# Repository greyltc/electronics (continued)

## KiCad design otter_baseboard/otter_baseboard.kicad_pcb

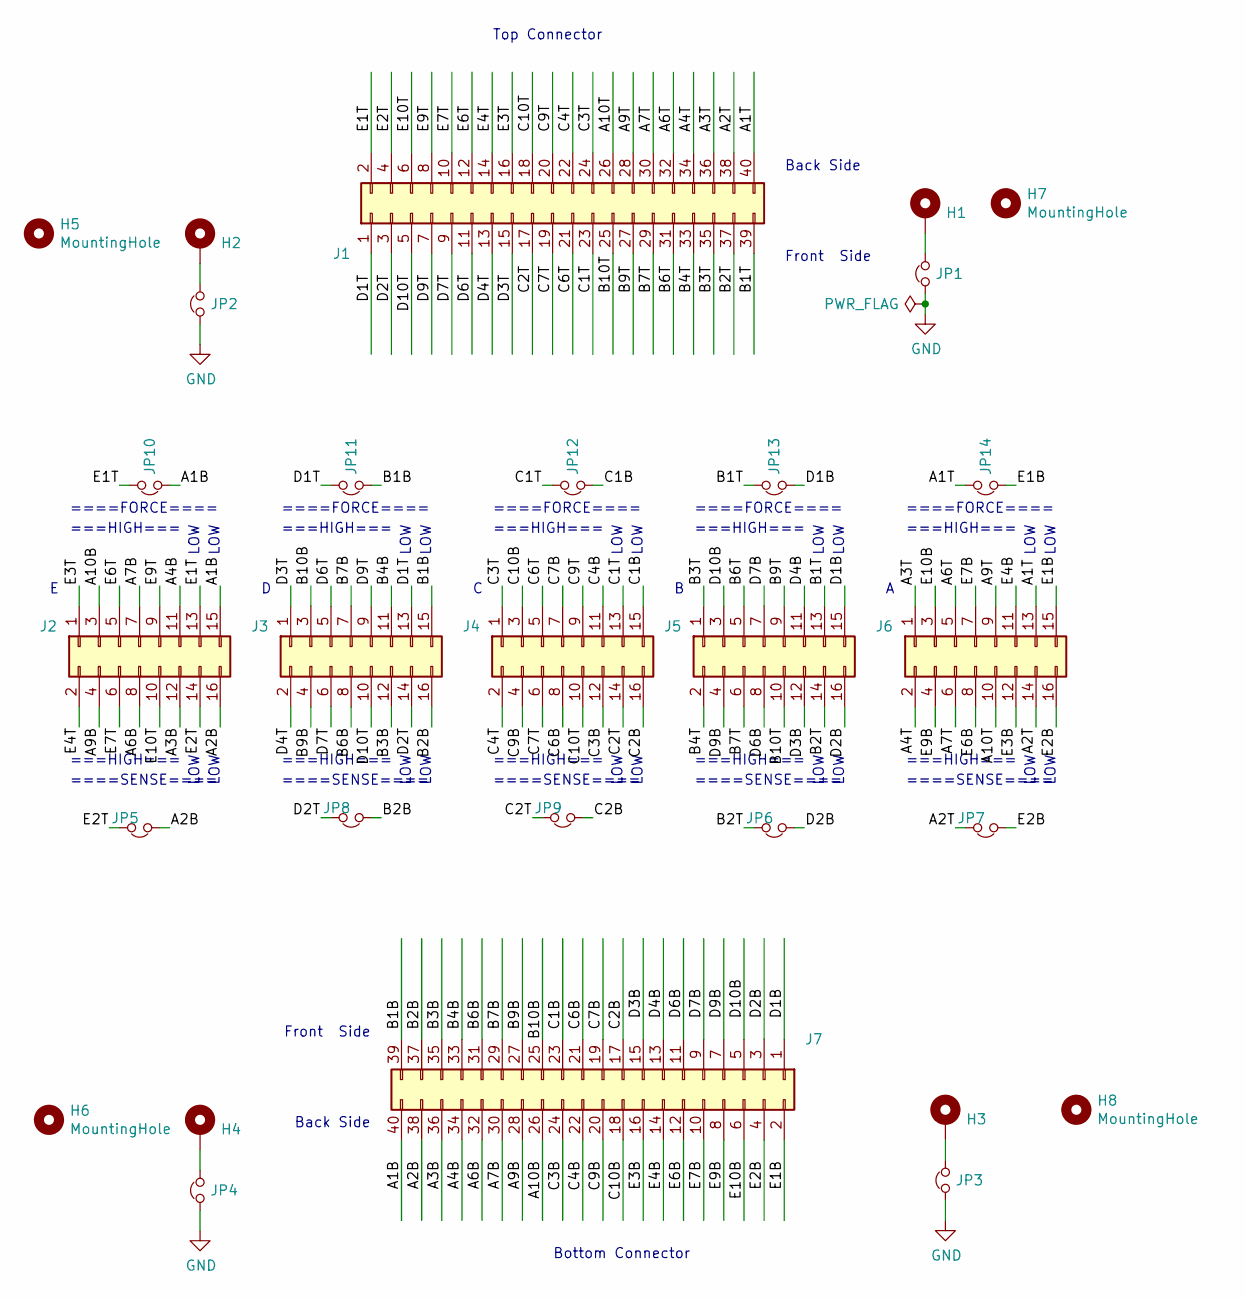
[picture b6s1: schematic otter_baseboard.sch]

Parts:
H1, H2, H3, H4: MountingHole_Pad; MountingHole_3.2mm_M3_ISO7380_Pad
H5, H6, H7, H8: MountingHole; MountingHole_6.4mm_M6
J1, J7: Conn_02x20_Odd_Even; Samtec_MECF-20-01-NP-L-DV-WT_2x20_P1.27mm_Socket_Horizontal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; mfg_part MECF-20-01-L-DV-NP-WT
J2, J3, J4, J5, J6: Conn_02x08_Odd_Even; PinHeader_2x08_P2.54mm_Vertical
JP1, JP2, JP3, JP4, JP5, JP6, JP7, JP8, JP9, JP10, JP11, JP12, JP13, JP14: Jumper_NC_Small; SolderJumper-2_P1.3mm_Bridged_RoundedPad1.0x1.5mm

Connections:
/A1B: J2.15, J7.40, JP10.2
/A1T: J1.40, J6.13, JP14.1
/A2B: J2.16, J7.38, JP5.2
/A2T: J1.38, J6.14, JP7.1
/A3B: J2.12, J7.36
/A3T: J1.36, J6.1
/A4B: J2.11, J7.34
/A4T: J1.34, J6.2
/A6B: J2.8, J7.32
/A6T: J1.32, J6.5
/A7B: J2.7, J7.30
/A7T: J1.30, J6.6
/A9B: J2.4, J7.28
/A9T: J1.28, J6.9
/A10B: J2.3, J7.26
/A10T: J1.26, J6.10
/B1B: J3.15, J7.39, JP11.2
/B1T: J1.39, J5.13, JP13.1
/B2B: J3.16, J7.37, JP8.2
/B2T: J1.37, J5.14, JP6.1
/B3B: J3.12, J7.35
/B3T: J1.35, J5.1
/B4B: J3.11, J7.33
/B4T: J1.33, J5.2
/B6B: J3.8, J7.31
/B6T: J1.31, J5.5
/B7B: J3.7, J7.29
/B7T: J1.29, J5.6
/B9B: J3.4, J7.27
/B9T: J1.27, J5.9
/B10B: J3.3, J7.25
/B10T: J1.25, J5.10
/C1B: J4.15, J7.23, JP12.2
/C1T: J1.23, J4.13, JP12.1
/C2B: J4.16, J7.17, JP9.2
/C2T: J1.17, J4.14, JP9.1
/C3B: J4.12, J7.24
/C3T: J1.24, J4.1
/C4B: J4.11, J7.22
/C4T: J1.22, J4.2
/C6B: J4.8, J7.21
/C6T: J1.21, J4.5
/C7B: J4.7, J7.19
/C7T: J1.19, J4.6
/C9B: J4.4, J7.20
/C9T: J1.20, J4.9
/C10B: J4.3, J7.18
/C10T: J1.18, J4.10
/D1B: J5.15, J7.1, JP13.2
/D1T: J1.1, J3.13, JP11.1
/D2B: J5.16, J7.3, JP6.2
/D2T: J1.3, J3.14, JP8.1
/D3B: J5.12, J7.15
/D3T: J1.15, J3.1
/D4B: J5.11, J7.13
/D4T: J1.13, J3.2
/D6B: J5.8, J7.11
/D6T: J1.11, J3.5
/D7B: J5.7, J7.9
/D7T: J1.9, J3.6
/D9B: J5.4, J7.7
/D9T: J1.7, J3.9
/D10B: J5.3, J7.5
/D10T: J1.5, J3.10
/E1B: J6.15, J7.2, JP14.2
/E1T: J1.2, J2.13, JP10.1
/E2B: J6.16, J7.4, JP7.2
/E2T: J1.4, J2.14, JP5.1
/E3B: J6.12, J7.16
/E3T: J1.16, J2.1
/E4B: J6.11, J7.14
/E4T: J1.14, J2.2
/E6B: J6.8, J7.12
/E6T: J1.12, J2.5
/E7B: J6.7, J7.10
/E7T: J1.10, J2.6
/E9B: J6.4, J7.8
/E9T: J1.8, J2.9
/E10B: J6.3, J7.6
/E10T: J1.6, J2.10
GND: JP1.1, JP2.1, JP3.1, JP4.1
unnamed: H1.1, JP1.2
unnamed: H2.1, JP2.2
unnamed: H3.1, JP3.2
unnamed: H4.1, JP4.2

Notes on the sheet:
LOW
====FORCE====
===HIGH===
====SENSE====
Front Side
Back Side
Bottom Connector
Top Connector

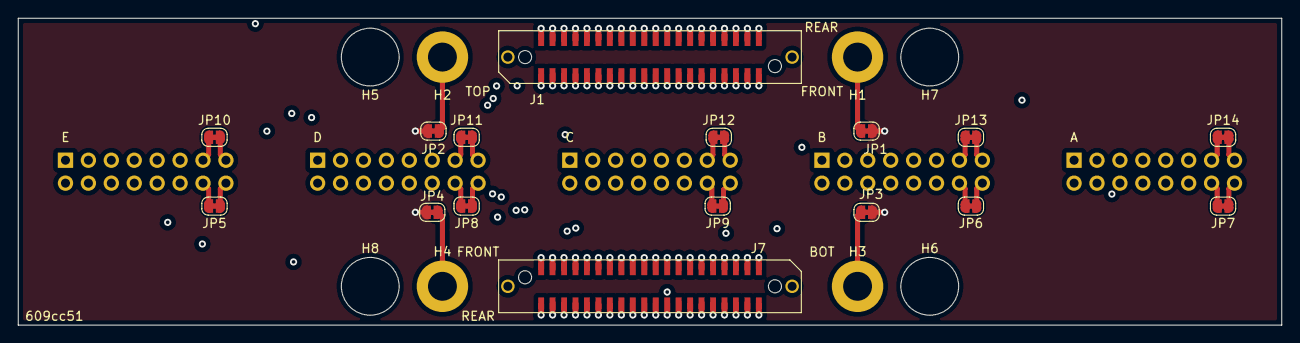
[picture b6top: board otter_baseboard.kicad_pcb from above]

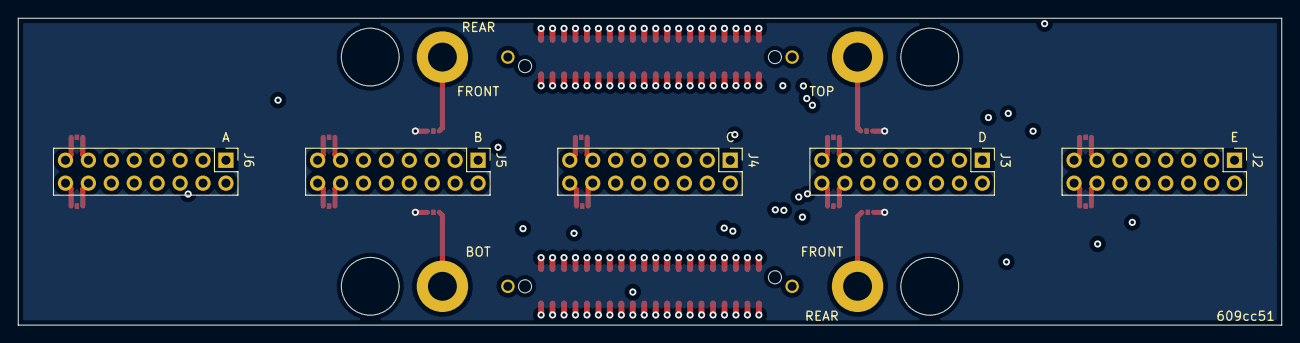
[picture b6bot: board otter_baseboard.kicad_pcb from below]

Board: 4 copper layers, 140.0 x 34.0 mm, 29 parts (5 on the bottom side), 85 nets.

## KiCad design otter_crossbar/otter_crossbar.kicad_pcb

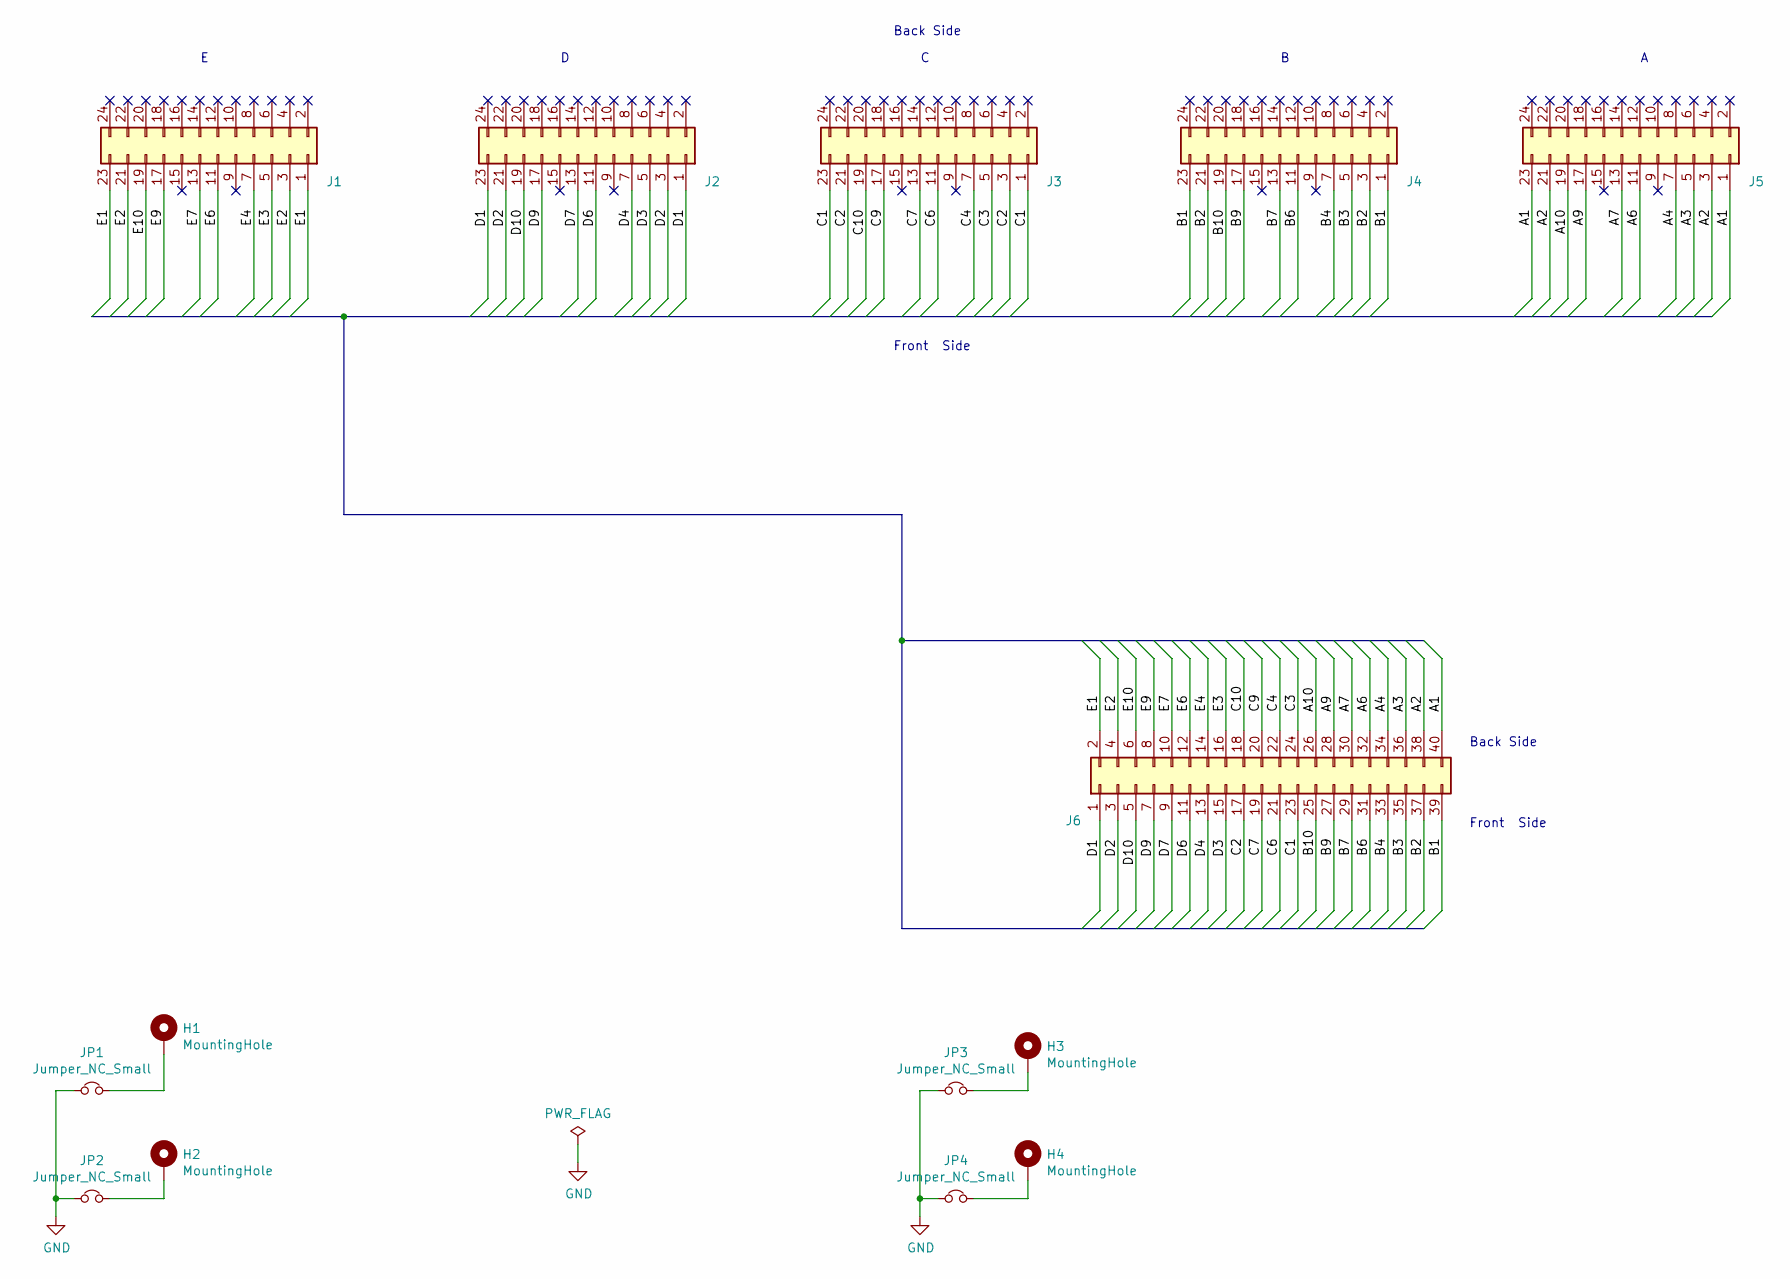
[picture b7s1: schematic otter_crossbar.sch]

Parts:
H1, H2, H3, H4: MountingHole; MountingHole_2.2mm_M2_Pad_Via
J1, J2, J3, J4, J5: Conn_02x12_Counter_Clockwise; PinSocket_2x12_P2.00mm_Vertical_EDGE; mfg_part SQT-112-03-F-D
J6: Conn_02x20_Odd_Even; Samtec_MECF-20-0_-NP-L-DV_2x20_P1.27mm_Edge_mod; mfg_part MECF-20-01-L-DV-NP-WT
JP1, JP2, JP3, JP4: Jumper_NC_Small; SolderJumper-2_P1.3mm_Bridged_RoundedPad1.0x1.5mm

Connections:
/A1: J5.1, J5.23, J6.40
/A2: J5.3, J5.21, J6.38
/A3: J5.5, J6.36
/A4: J5.7, J6.34
/A6: J5.11, J6.32
/A7: J5.13, J6.30
/A9: J5.17, J6.28
/A10: J5.19, J6.26
/B1: J4.1, J4.23, J6.39
/B2: J4.3, J4.21, J6.37
/B3: J4.5, J6.35
/B4: J4.7, J6.33
/B6: J4.11, J6.31
/B7: J4.13, J6.29
/B9: J4.17, J6.27
/B10: J4.19, J6.25
/C1: J3.1, J3.23, J6.23
/C2: J3.3, J3.21, J6.17
/C3: J3.5, J6.24
/C4: J3.7, J6.22
/C6: J3.11, J6.21
/C7: J3.13, J6.19
/C9: J3.17, J6.20
/C10: J3.19, J6.18
/D1: J2.1, J2.23, J6.1
/D2: J2.3, J2.21, J6.3
/D3: J2.5, J6.15
/D4: J2.7, J6.13
/D6: J2.11, J6.11
/D7: J2.13, J6.9
/D9: J2.17, J6.7
/D10: J2.19, J6.5
/E1: J1.1, J1.23, J6.2
/E2: J1.3, J1.21, J6.4
/E3: J1.5, J6.16
/E4: J1.7, J6.14
/E6: J1.11, J6.12
/E7: J1.13, J6.10
/E9: J1.17, J6.8
/E10: J1.19, J6.6
GND: JP1.1, JP2.1, JP3.1, JP4.1
unnamed: H1.1, JP1.2
unnamed: H2.1, JP2.2
unnamed: H3.1, JP3.2
unnamed: H4.1, JP4.2

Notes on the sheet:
Front Side
Back Side

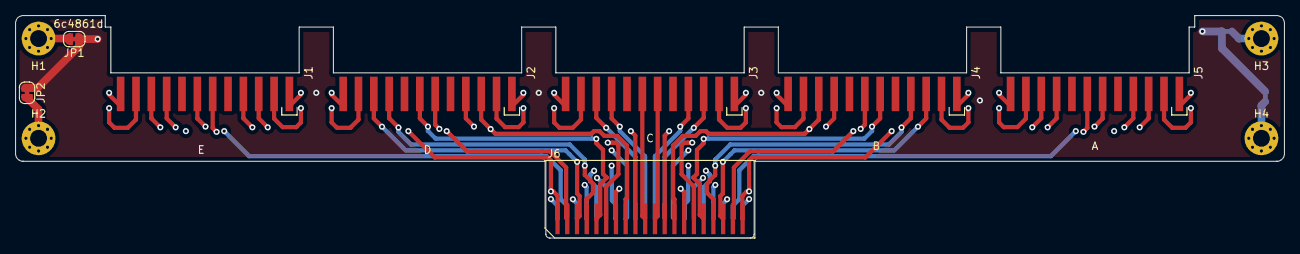
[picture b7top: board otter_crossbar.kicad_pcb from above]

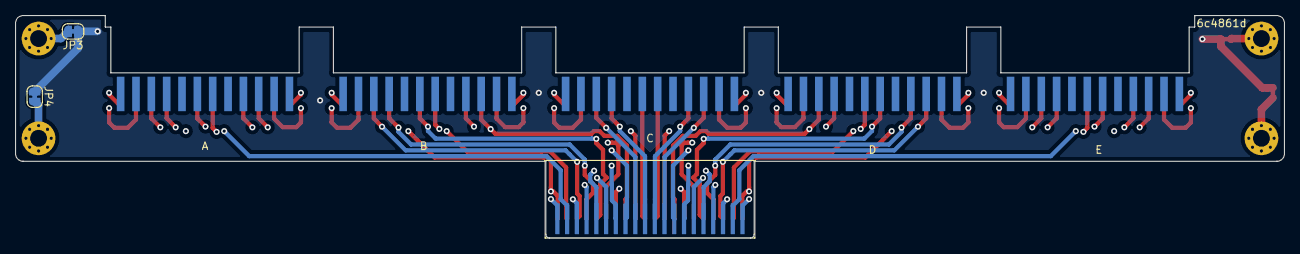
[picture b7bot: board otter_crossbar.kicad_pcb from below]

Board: 4 copper layers, 165.4 x 29.0 mm, 14 parts (2 on the bottom side), 45 nets.

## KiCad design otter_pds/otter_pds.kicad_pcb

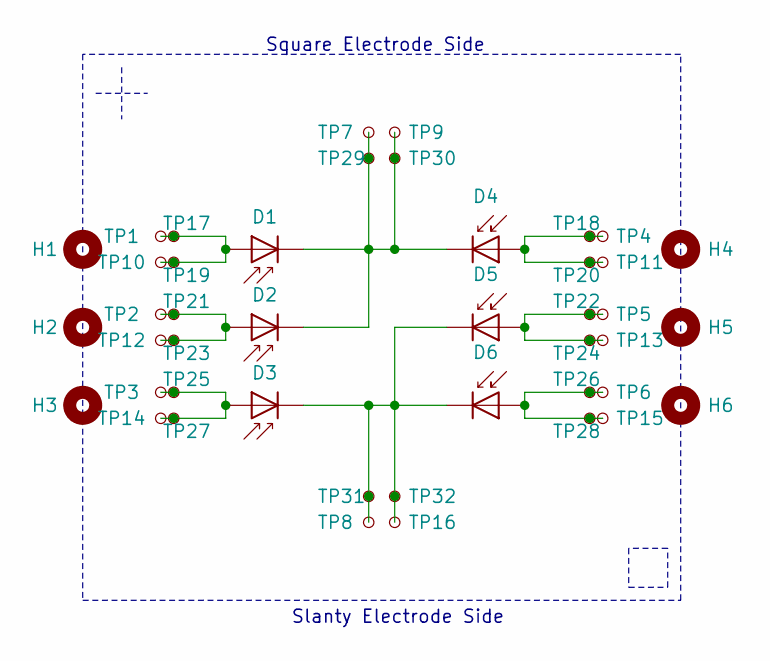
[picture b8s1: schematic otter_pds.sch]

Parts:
D1, D2, D3, D4, D5, D6: D_Photo; BPW34
H1, H2, H3, H4, H5, H6: MountingHole; MountingHole_2.7mm
TP1, TP2, TP3, TP4, TP5, TP6, TP7, TP8, TP9, TP10, TP11, TP12, TP13, TP14, TP15, TP16, TP17, TP18, TP19, TP20, TP21, TP22, TP23, TP24, TP25, TP26, TP27, TP28, TP29, TP30, TP31, TP32: TestPoint_Small; TestPoint_Pad_D2.0mm

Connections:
unnamed: D1.1 (K), D2.1 (K), D4.1 (K), TP7.1, TP9.1, TP29.1, TP30.1
unnamed: D1.2 (A), TP1.1, TP10.1, TP17.1, TP19.1
unnamed: D2.2 (A), TP2.1, TP12.1, TP21.1, TP23.1
unnamed: D3.1 (K), D5.1 (K), D6.1 (K), TP8.1, TP16.1, TP31.1, TP32.1
unnamed: D3.2 (A), TP3.1, TP14.1, TP25.1, TP27.1
unnamed: D4.2 (A), TP4.1, TP11.1, TP18.1, TP20.1
unnamed: D5.2 (A), TP5.1, TP13.1, TP22.1, TP24.1
unnamed: D6.2 (A), TP6.1, TP15.1, TP26.1, TP28.1

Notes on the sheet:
Slanty Electrode Side
Square Electrode Side

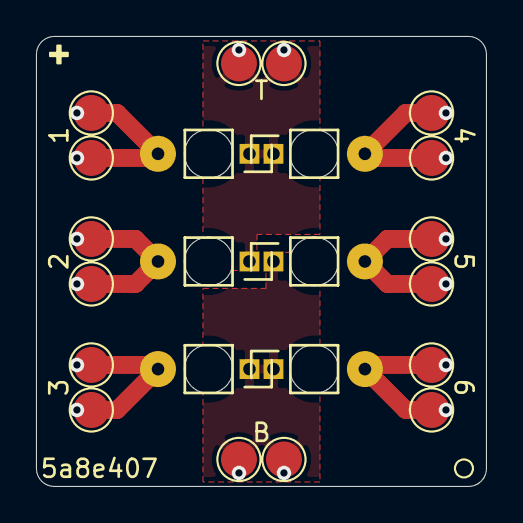
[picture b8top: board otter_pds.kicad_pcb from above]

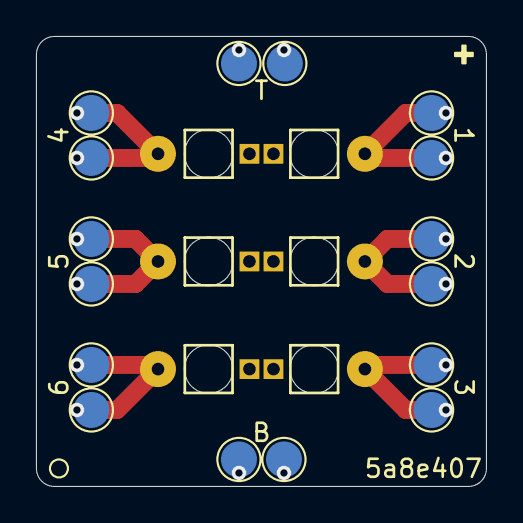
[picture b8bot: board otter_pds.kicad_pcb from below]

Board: 2 copper layers, 25.0 x 25.0 mm, 44 parts (16 on the bottom side), 8 nets.
